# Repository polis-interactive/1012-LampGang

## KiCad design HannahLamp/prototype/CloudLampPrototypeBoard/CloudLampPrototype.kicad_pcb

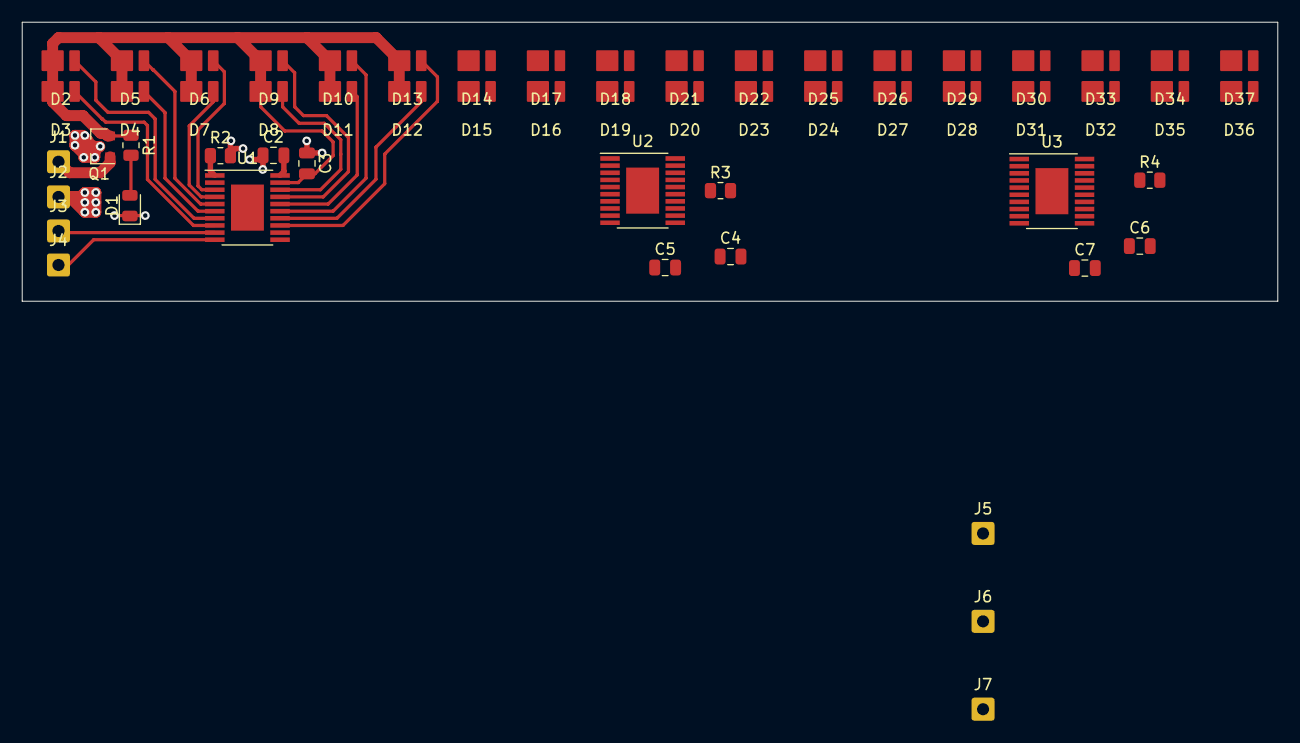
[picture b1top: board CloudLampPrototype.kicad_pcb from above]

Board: 2 copper layers, 114.3 x 25.4 mm, 58 parts (0 on the bottom side), 54 nets.

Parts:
C2, C4, C6: 1u; C_0805_2012Metric
C3, C5, C7: 0.1u; C_0805_2012Metric
D1: LED; LED_0805_2012Metric
D2, D4, D6, D8, D10, D12, D14, D16, D18, D20, D22, D24, D26, D28, D30, D32, D34, D36: WW; Luxeon_2835
D3, D5, D7, D9, D11, D13, D15, D17, D19, D21, D23, D25, D27, D29, D31, D33, D35, D37: CW; Luxeon_2835
J1: V+; SolderWire-0.5sqmm_1x01_D0.9mm_OD2.1mm
J2, J5: GND; SolderWire-0.5sqmm_1x01_D0.9mm_OD2.1mm
J3, J6: Data; SolderWire-0.5sqmm_1x01_D0.9mm_OD2.1mm
J4, J7: Clock; SolderWire-0.5sqmm_1x01_D0.9mm_OD2.1mm
Q1: Reverse P; SOT-23
R1: 8.4k; R_0805_2012Metric
R2, R3, R4: 0.827K; R_0805_2012Metric
U1, U2, U3: TLC5971PWP; Texas_PWP0020A

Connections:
12vRaw: J1.1, Q1.1
+12V: C3.2, C5.2, C7.2, D2.2, D3.2, D4.2, D5.2, D6.2, D7.2, D8.2, D9.2, D10.2, D11.2, D12.2, D13.2, D14.2, D15.2, D16.2, D17.2, D18.2, D19.2, D20.2, D21.2, D22.2, D23.2, D24.2, D25.2, D26.2, D27.2, D28.2, D29.2, D30.2, D31.2, D32.2, D33.2, D34.2, D35.2, D36.2, D37.2, Q1.2, R1.1, U1.19, U2.19, U3.19
CW_0: D3.1, U1.8
CW_1: D5.1, U1.5
CW_2: D7.1, U1.4
CW_3: D9.1, U1.17
CW_4: D11.1, U1.16
CW_5: D13.1, U1.13
CW_6: D15.1, U2.4
CW_7: D17.1, U2.6
CW_8: D19.1, U2.8
CW_9: D21.1, U2.14
CW_10: D23.1, U2.16
CW_11: D25.1, U2.18
CW_12: D27.1, U3.4
CW_13: D29.1, U3.6
CW_14: D31.1, U3.8
CW_15: D33.1, U3.14
CW_16: D35.1, U3.16
CW_17: D37.1, U3.18
Clock_1: U1.12, U2.10
Clock_2: U2.12, U3.10
Clock_In: J4.1, U1.10
Clock_Out: J7.1, U3.12
Data_1: U1.11, U2.9
Data_2: U2.11, U3.9
Data_In: J3.1, U1.9
Data_Out: J6.1, U3.11
GND: C2.1, C3.1, C4.1, C5.1, C6.1, C7.1, D1.1, J2.1, J5.1, Q1.3, R2.2, R3.2, R4.2, U1.2, U1.21, U2.2, U2.21, U3.2, U3.21
unnamed: C2.2, U1.20
unnamed: C4.2, U2.20
unnamed: C6.2, U3.20
unnamed: D1.2, R1.2
unnamed: R2.1, U1.1
unnamed: R3.1, U2.1
unnamed: R4.1, U3.1
WW_0: D2.1, U1.7
WW_1: D4.1, U1.6
WW_2: D6.1, U1.3
WW_3: D8.1, U1.18
WW_4: D10.1, U1.15
WW_5: D12.1, U1.14
WW_6: D14.1, U2.3
WW_7: D16.1, U2.5
WW_8: D18.1, U2.7
WW_9: D20.1, U2.13
WW_10: D22.1, U2.15
WW_11: D24.1, U2.17
WW_12: D26.1, U3.3
WW_13: D28.1, U3.5
WW_14: D30.1, U3.7
WW_15: D32.1, U3.13
WW_16: D34.1, U3.15
WW_17: D36.1, U3.17
